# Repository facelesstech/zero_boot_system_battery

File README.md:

# zero_boot_system_battery
zero_boot_system_battery

Youtube - https://www.youtube.com/watch?v=CKD1gWXzSro
Blog post - https://facelesstech.wordpress.com/2018/11/05/pi-boot-system/

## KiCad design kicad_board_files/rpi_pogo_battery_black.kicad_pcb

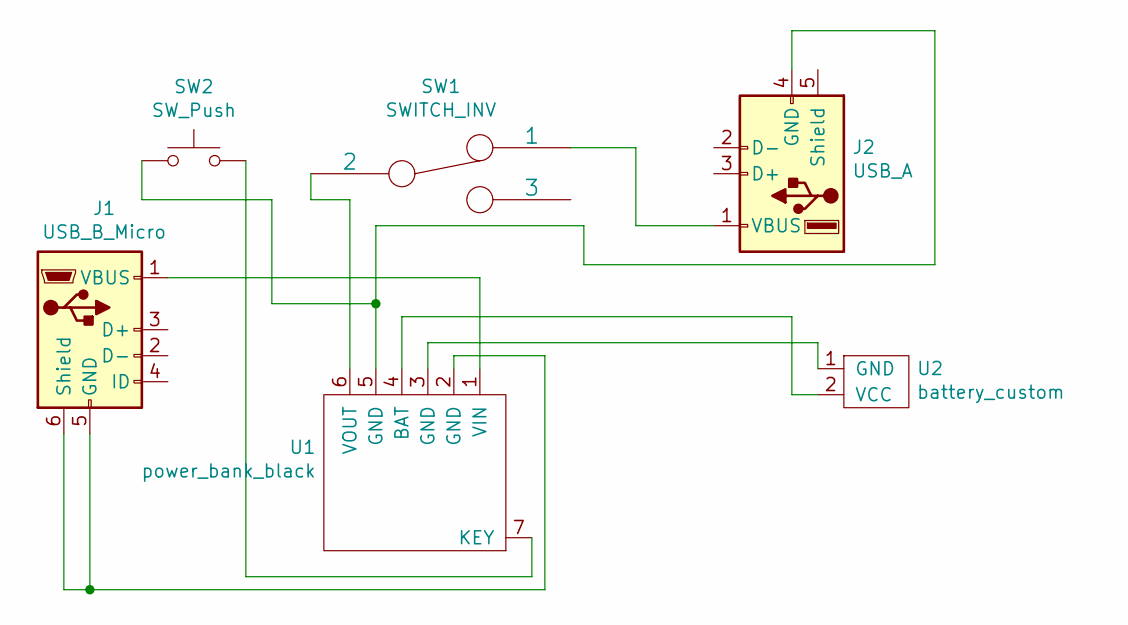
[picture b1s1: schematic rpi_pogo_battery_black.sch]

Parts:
J1: USB_B_Micro; USB_Micro-B_Molex-105017-0001
J2: USB_A; raspberry_pi_zero_otg
SW1: SWITCH_INV; 3_pin_switch_custom
SW2: SW_Push; small_button_2pin_custom
U1: power_bank_black
U2: battery_custom; jst_2pin_custom

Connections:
unnamed: J1.1 (VBUS), U1.1 (VIN)
unnamed: J1.5 (GND), J1.6 (Shield), U1.2 (GND)
unnamed: J2.1 (VBUS), SW1.1
unnamed: J2.4 (GND), SW2.1, U1.5 (GND)
unnamed: SW1.2, U1.6 (VOUT)
unnamed: SW2.2, U1.7 (KEY)
unnamed: U1.3 (GND), U2.1 (GND)
unnamed: U1.4 (BAT), U2.2 (VCC)

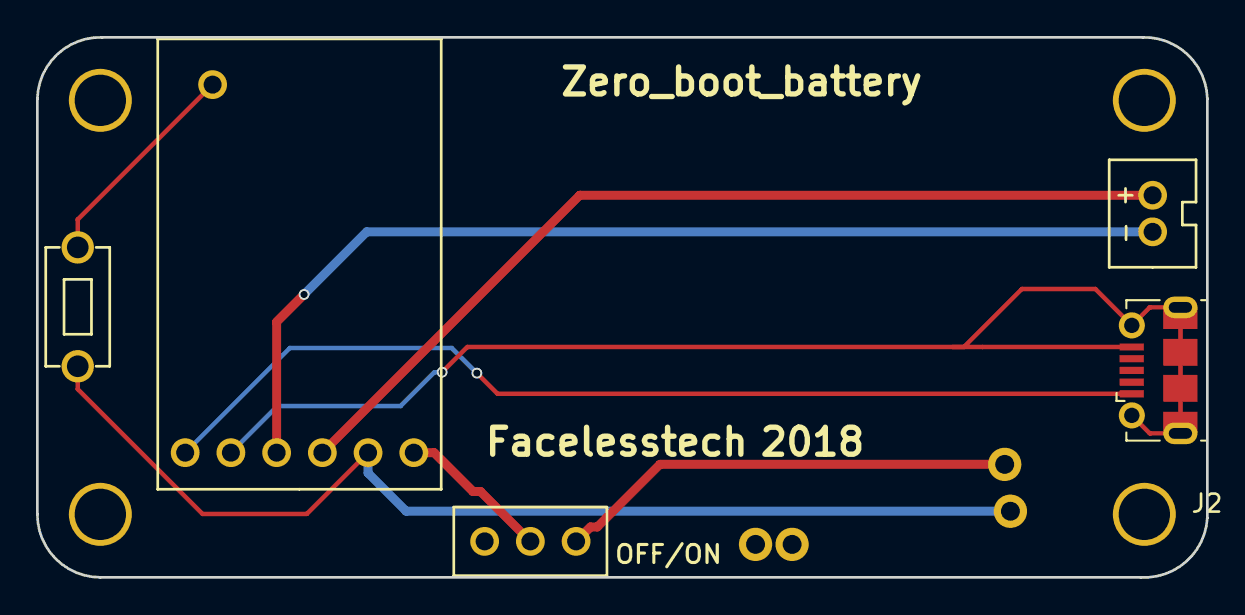
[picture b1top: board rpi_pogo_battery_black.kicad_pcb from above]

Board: 2 copper layers, 65.0 x 30.0 mm, 6 parts (0 on the bottom side), 8 nets.

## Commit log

2019-02-03 board files
2019-02-03 added links
